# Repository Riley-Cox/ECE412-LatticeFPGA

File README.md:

# ECE412-LatticeFPGA
## WSL Setup
- Install the Terminal app on the Microsoft Store
- Install a Linux Distribution from the Microsoft Store, Debian was used for this project
- Install usbipd through PowerShell by using the following command
  
  ```
  winget install --interactive --exact dorssel.usbipd-win
  ```
- To ensure that it is installed run `usbipd list` , you should see your usb device with its BusID (the UPduino should show up as "serial converter")
- A USB bind is needed. Open Powershell as Admin, then run `usbipd bind --busid <busid>`
- To attach a USB to WSL run `usbipd attach --wsl --busid <busid>`
- In WSL, the device should show up when `lsusb` is ran, if the command is not found run  `sudo apt-get install usbutils `
- To disconnect the device run `usbipd detach --busid <busid>`

## Dependencies
### Ubuntu/Debian
```
sudo apt-get install autoconf automake autotools-dev curl python3 python3-pip python3-tomli libmpc-dev libmpfr-dev libgmp-dev gawk build-essential bison flex texinfo gperf libtool patchutils bc zlib1g-dev libexpat-dev ninja-build git cmake libglib2.0-dev libslirp-dev xxd make
```
### Fedora
```
sudo yum install autoconf automake python3 libmpc-devel mpfr-devel gmp-devel gawk  bison flex texinfo patchutils gcc gcc-c++ zlib-devel expat-devel libslirp-devel xxd make
```
### Arch
```
sudo pacman -Syu autoconf automake curl python3 libmpc mpfr gmp gawk base-devel bison flex texinfo gperf libtool patchutils bc zlib expat libslirp xxd make
```
## RISC-V GNU Toolchain
- From your home directory, clone the RISC-V GNU toolchain from the following repo 

  ```
  git clone https://github.com/riscv/riscv-gnu-toolchain
  ```

- From your home directory, open your shell rc file to edit (`vim .zshrc` or `vim .bashrc`) and add
  ```
  export PATH="<writeable directory>:$PATH"
  ```
  Note that the path you choose for the `<writeable directory>` should end with /bin
  
  Ex: `export PATH="$HOME/Documents/riscv-toolchain/bin:$PATH"`
- Then run `source .zshrc` if using zsh or `source .bashrc` if using bash
  
- `cd` into the riscv-gnu-toolchain directory, run
  ```
  ./configure --prefix=<writeable directory>
  ```
  Note that this `<writeable directory>` does not need to include /bin
  
  Ex: `./configure --prefix=$HOME/Documents/riscv-toolchain`
- then run `make`

## Open Source Toolchain Setup
### Ubuntu/Debian
```
sudo apt-get install yosys fpga-icestorm nextpnr-ice40-qt
```
### Arch
```
yay -S yosys-git icestorm-git nextpnr-git
```
### Fedora
```
sudo dnf install yosys icestorm nextpnr
```

## Building on the UPduino board
- Clone this repo
  ```
  git clone https://github.com/Riley-Cox/ECE412-LatticeFPGA.git
  ```
  
- Navigate to `ECE412-LatticeFPGA/V2.1/src/icicle` 
- Run `make clean`
- Run `make BOARD=upduino`
- Run `sudo iceprog top.bin`

## Migrating Icicle from UPduino V1 to V2.1
- Removed SPI_FLASH define from the upduino-defines.sv file located in `/icicle/boards`
- Changed PROGMEM value from flash to ram in the upduino.mk file located in `/icicle/boards`
- Changed UART RX/TX pins to 15 and 14 respectively in the upduino.pcf file located in `/icicle/boards`
- Created a flash_csn output in icicle.sv and assign it 1 (`assign flash_csn = 1`)

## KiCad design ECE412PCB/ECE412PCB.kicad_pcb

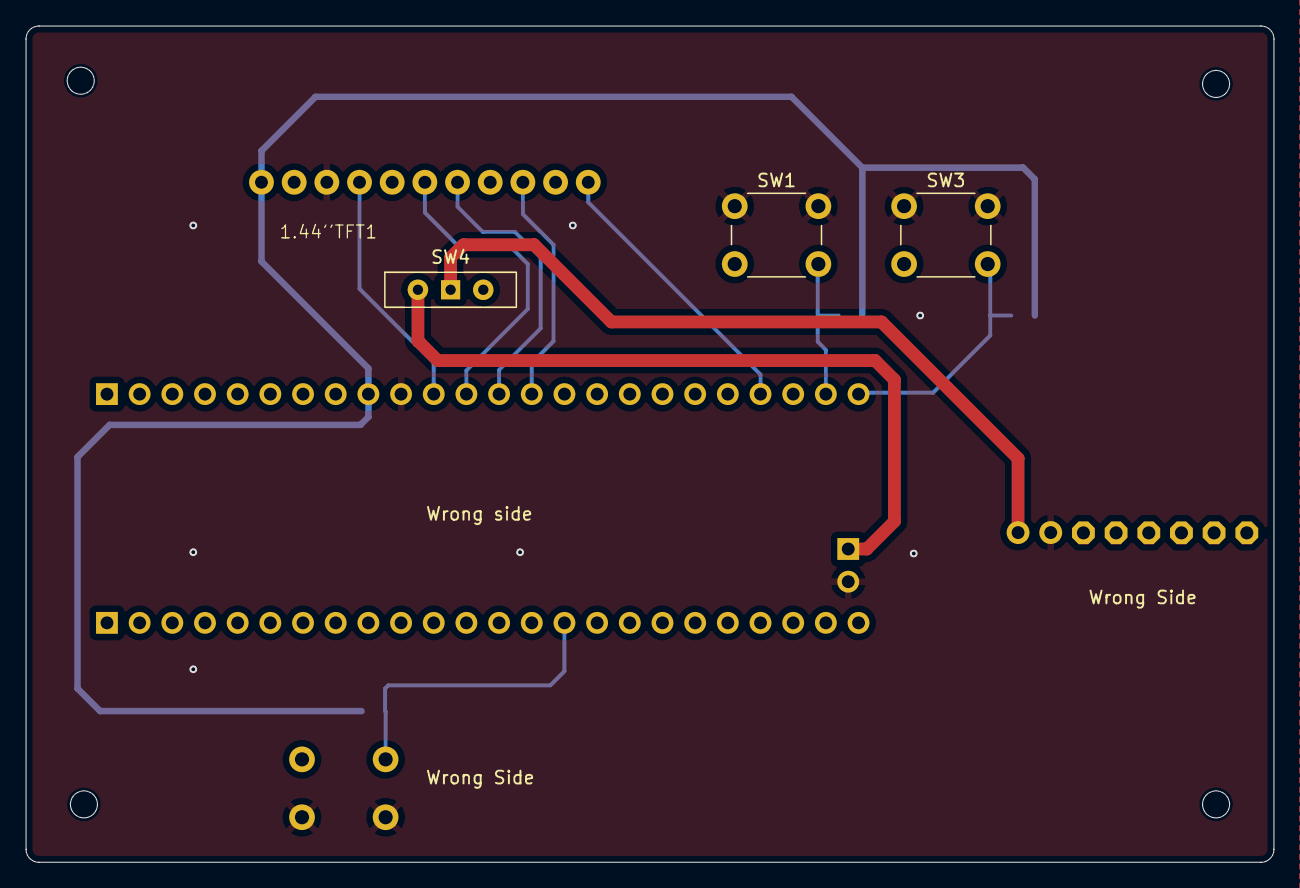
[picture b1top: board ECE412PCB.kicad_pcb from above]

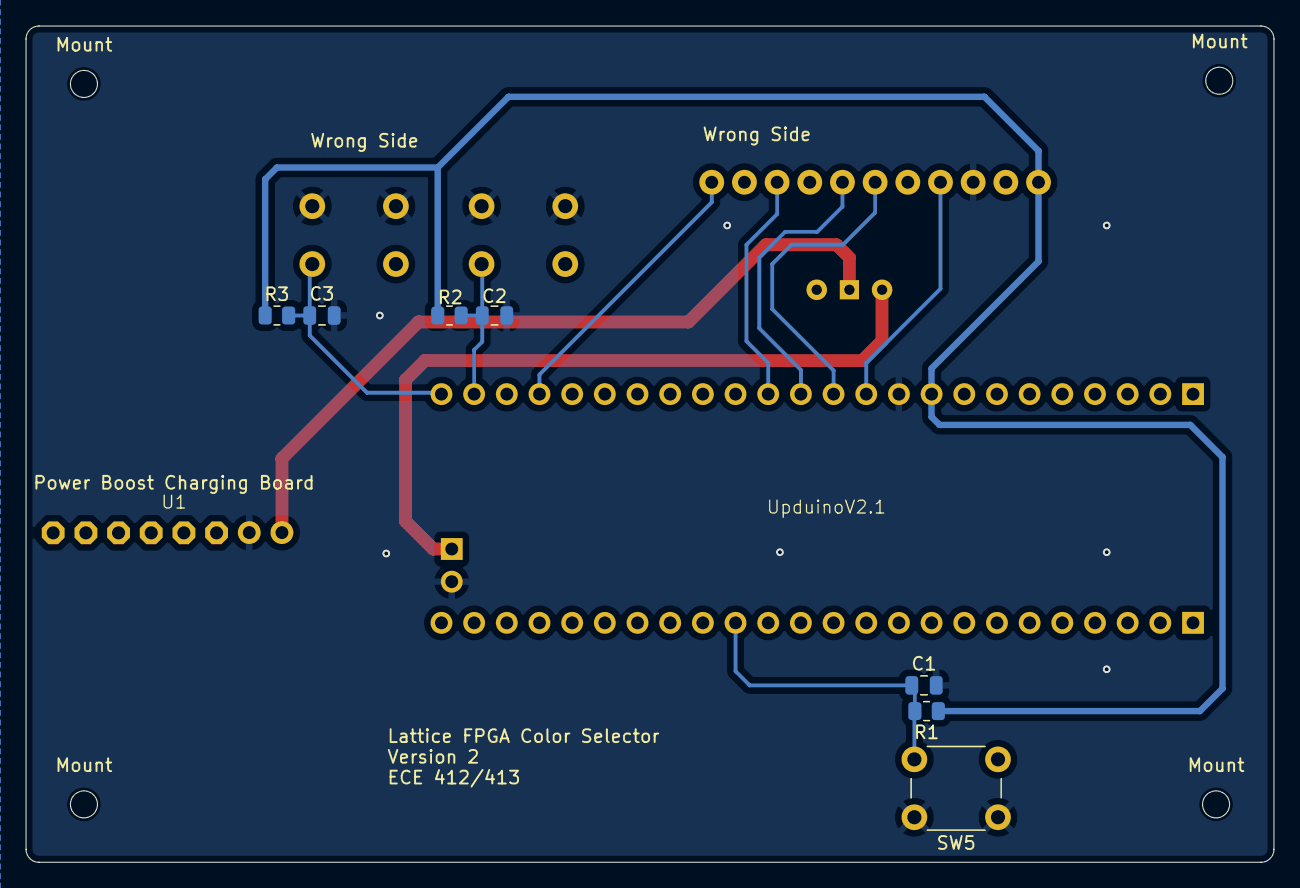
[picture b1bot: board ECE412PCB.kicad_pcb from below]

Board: 2 copper layers, 97.0 x 65.0 mm, 17 parts (9 on the bottom side), 12 nets.

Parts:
1.44''TFT1: 1.44_ TFT Display
C1, C2, C3: C; C_0805_2012Metric
Mount: MountingHole_2.1mm
Mount#2, Mount#3, Mount#4: MountingHole_2.1mm
R1, R2, R3: R; R_0805_2012Metric
SW1, SW3, SW5: SW_Push; SW_PUSH_6mm
SW4: Board Power; SW_Slide-03_Wuerth-WS-SLTV_10x2.5x6.4_P2.54mm
U1: Power Boost Charging Board; PowerBoost-500
UpduinoV2.1: UPduinoV3.1

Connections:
+3.3V: 1.44''TFT1.1 (Vin), R1.1, R2.1, R3.1, UpduinoV2.1.19 (3.3V)
+5V: SW4.1 (A), U1.1 (5V)
/CS: 1.44''TFT1.7 (TCS), UpduinoV2.1.23 (26)
/ColorPush: C2.1, R2.2, SW1.2, UpduinoV2.1.33 (38)
/DC: 1.44''TFT1.9 (D/C), UpduinoV2.1.24 (27)
/LITE: 1.44''TFT1.11 (Lite), UpduinoV2.1.31 (35)
/MOSI: 1.44''TFT1.6 (SI), UpduinoV2.1.22 (25)
/Reset: C1.1, R1.2, SW5.2, UpduinoV2.1.9
/SCK: 1.44''TFT1.4 (SCK), UpduinoV2.1.21 (23)
/brightPush: C3.1, R3.2, SW3.2, UpduinoV2.1.34 (28)
GND: 1.44''TFT1.3 (Gnd), C1.2, C2.2, C3.2, SW1.1, SW3.1, SW5.1, U1.2 (GND), UpduinoV2.1.20 (GND), UpduinoV2.1.35 (GND)
unnamed: SW4.2 (B), UpduinoV2.1.36 (5V)

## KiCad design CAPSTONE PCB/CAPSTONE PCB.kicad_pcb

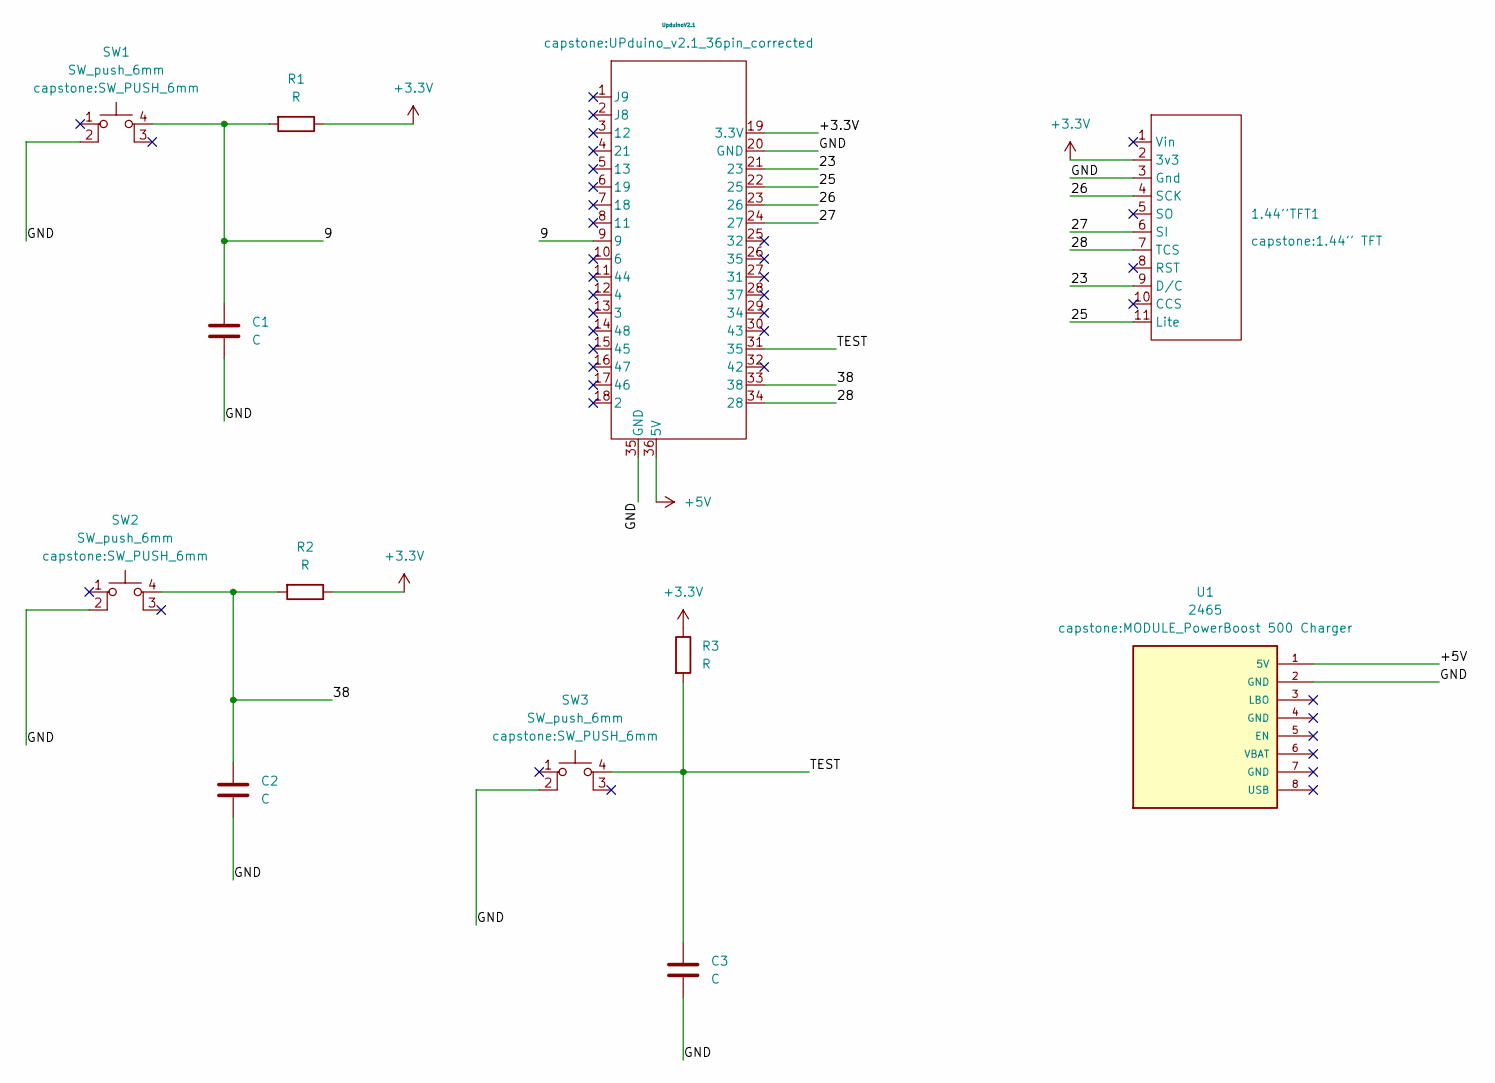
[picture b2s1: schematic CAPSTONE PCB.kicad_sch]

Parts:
1.44''TFT1: 1.44'' TFT
C1, C2, C3: C; C_Axial_L3.8mm_D2.6mm_P7.50mm_Horizontal
R1, R2, R3: R; R_Axial_DIN0207_L6.3mm_D2.5mm_P2.54mm_Vertical
SW1, SW2, SW3: SW_push_6mm; SW_PUSH_6mm
U1: 2465; MODULE_PowerBoost 500 Charger; PARTREV B
UpduinoV2.1: UPduino_v2.1_36pin_corrected

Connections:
+3.3V: 1.44''TFT1.2 (3v3), R1.1, R2.1, R3.1, UpduinoV2.1.19 (3.3V)
+5V: U1.1 (5V), UpduinoV2.1.36 (5V)
/9: C1.1, R1.2, SW1.4 (A), UpduinoV2.1.9
/23: 1.44''TFT1.9 (D/C), UpduinoV2.1.21 (23)
/25: 1.44''TFT1.11 (Lite), UpduinoV2.1.22 (25)
/26: 1.44''TFT1.4 (SCK), UpduinoV2.1.23 (26)
/27: 1.44''TFT1.6 (SI), UpduinoV2.1.24 (27)
/28: 1.44''TFT1.7 (TCS), UpduinoV2.1.34 (28)
/38: C2.1, R2.2, SW2.4 (A), UpduinoV2.1.33 (38)
/GND: 1.44''TFT1.3 (Gnd), C1.2, C2.2, C3.2, SW1.2, SW2.2, SW3.2, U1.2 (GND), UpduinoV2.1.20 (GND), UpduinoV2.1.35 (GND)
/TEST: C3.1, R3.2, SW3.4 (A), UpduinoV2.1.31 (35)

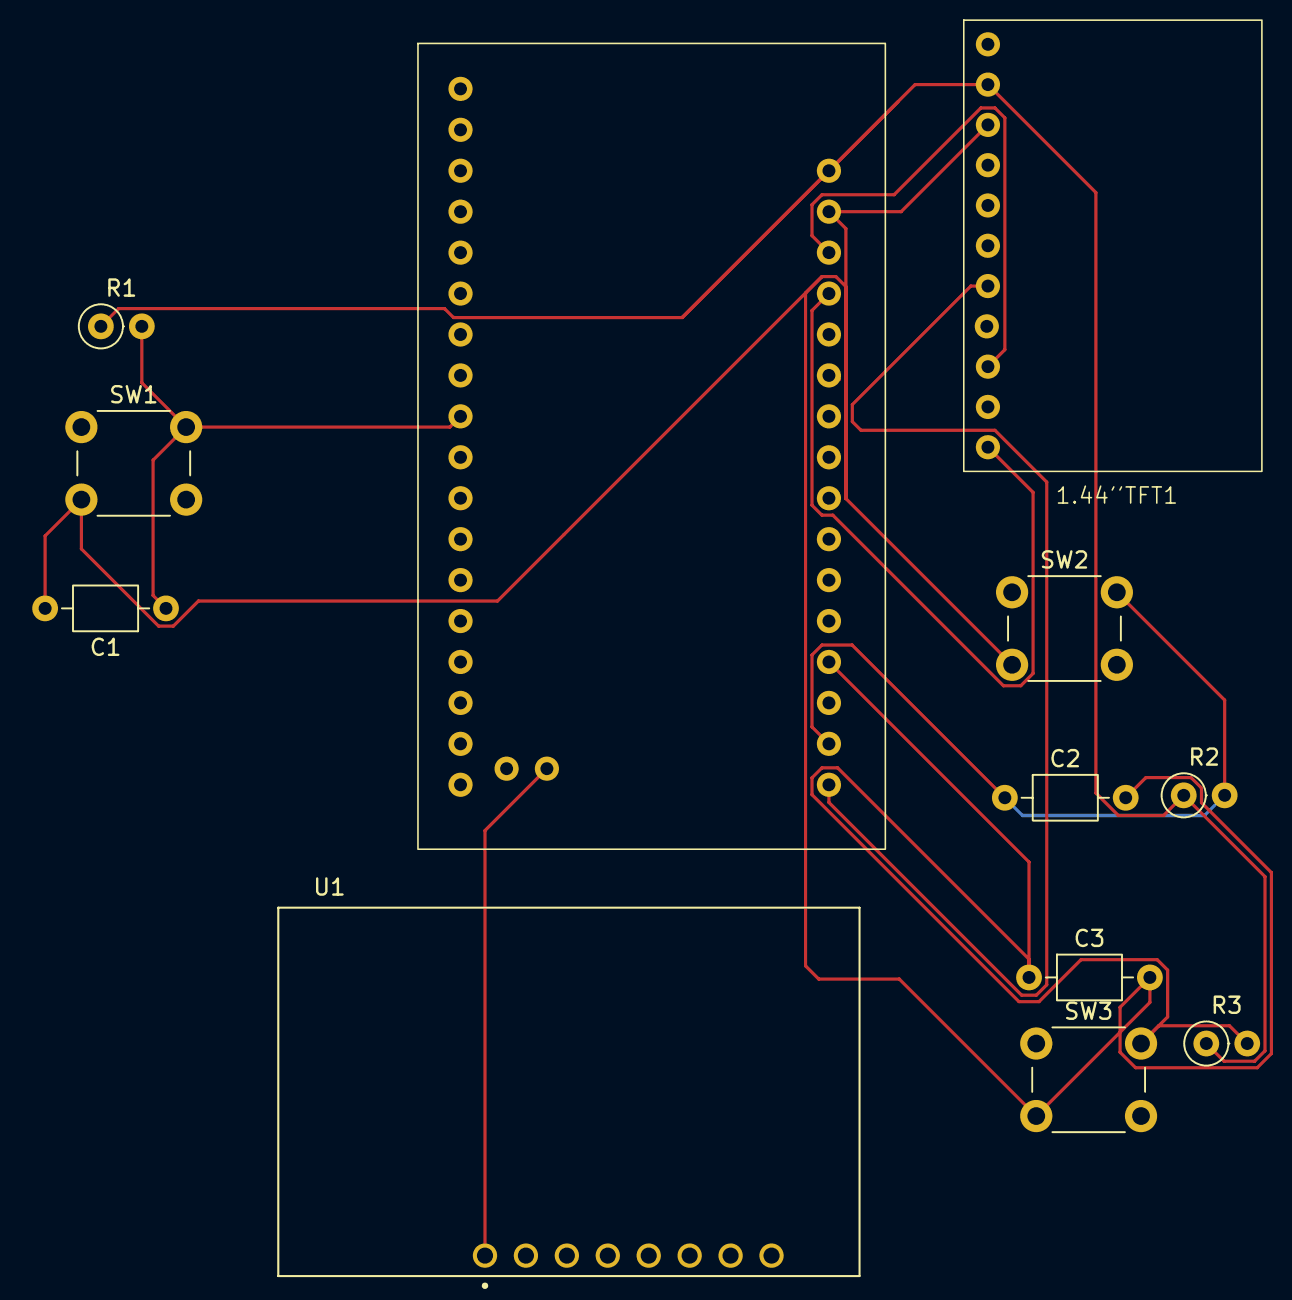
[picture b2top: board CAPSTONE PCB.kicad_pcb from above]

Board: 2 copper layers, 12 parts (0 on the bottom side), 11 nets.

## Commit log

2025-01-20 Weekly Report set up
    Include temple from Andrew, and weekly report. Delete the gray text while finished.
2025-01-20 Set up documents
    Project description and Team Contract
2025-01-20 Create Friday_Jan_17_2025_Meeting_Notes.md
    Added the meeting notes for our initial meeting with Rahul
2025-01-20 Update Friday_Jan_17_2025_Meeting_Notes.md
    Attempting to fix formatting issues
2025-01-20 Update Friday_Jan_17_2025_Meeting_Notes.md
    Fixed remaining formatting issues
2025-01-20 Update Friday_Jan_17_2025_Meeting_Notes.md
    further fix attempted for bullet points
2025-01-20 Update Friday_Jan_17_2025_Meeting_Notes.md
    Final Fix to attendance bullet points
2025-01-20 Adding Meeting Notes (#1)
    * Create Friday_Jan_17_2025_Meeting_Notes.md
    Added the meeting notes for our initial meeting with Rahul
    * Update Friday_Jan_17_2025_Meeting_Notes.md
    Attempting to fix formatting issues
    * Update Friday_Jan_17_2025_Meeting_Notes.md
    Fixed remaining formatting issues
2025-01-24 Added preliminary gannt chart to repo
    *SUBJECT TO CHANGE*
2025-01-24 add rough draft of project proposal
    proposal version 0.1
2025-01-25 Mohammad edits (#2)
    * Create Friday_Jan_17_2025_Meeting_Notes.md
    Added the meeting notes for our initial meeting with Rahul
    * Update Friday_Jan_17_2025_Meeting_Notes.md
    Attempting to fix formatting issues
    * Update Friday_Jan_17_2025_Meeting_Notes.md
    Fixed remaining formatting issues
2025-02-02 Update README.md
    Added changes that need to be made to make Icicle RISC-V core work on UPduino V2.1
2025-02-02 Update README.md (#3)
    Added changes that need to be made to make Icicle RISC-V core work on UPduino V2.1
2025-02-03 Added UPduino V2.1 migration for icicle, now able to build on V2.1 and use serial monitor
2025-02-03 Trying to fix issue
2025-02-03 Adding icicle files
2025-02-08 Create TODO
2025-02-08 Create TODO (#5)
2025-02-10 Update TODO
2025-02-11 Update TODO (#7)
2025-02-11 Update README.md
    Added the ability to copy the long dependency packages and removed the install make and riscv-unknown-elf from the "other dependencies" section. Added make to "Dependencies"
2025-02-17 Create 17FEB2025
    Meeting notes
2025-02-17 Create 17FEB2025 (#9)
    Meeting notes
2025-02-20 Set of param
2025-02-20 Fixed
2025-02-20 Formatted
2025-02-20 Doc sync
2025-02-21 Create 21FEB2025
2025-02-23 3D printing
2025-02-23 Create 21FEB2025 (#10)
2025-02-24 Create 24FEB2025
2025-02-24 Create 24FEB2025 (#11)
2025-02-26 Create testbench_notSyn
2025-02-28 Create 28FEB2025
2025-03-01 Create 28FEB2025 (#13)
2025-03-03 Create 03MAR2025
2025-03-04 Create 03MAR2025 (#14)
2025-03-07 Text display
2025-03-07 Create 07MAR2025
2025-03-08 Update Top_module_spi.sv
    added buffer and clock generation through HSOSC primitive
2025-03-10 Driver code in C, version 0.1
    The first version of code, the values and address in hw.h should be changed based on real hardware
2025-03-10 Create 07MAR2025 (#15)
2025-03-10 Create 10MAR2025
2025-03-10 Update 10MAR2025
2025-03-14 Create 14MAR2025
2025-03-20 Weekly Report updates
2025-03-21 Weekly Reports
2025-03-24 Create 24MAR2025
2025-03-24 Create 14MAR2025 (#16)
2025-03-24 Added yosys changes for spi
2025-03-25 testing file management
2025-03-25 Test didn't work
2025-03-25 Adding in peripheral modules and testbench
2025-03-25 Better yosys synth commands
2025-03-25 Radiant mods
2025-03-26 Create 26MAR2025
2025-03-26 Yosys PLL
2025-03-27 Create 31JAN2025
2025-03-27 Create 13FEB2025
2025-03-27 Create 03FEB2025
2025-03-27 Create 27JAN2025
2025-03-27 Changed Top_module_spi.sv to the version succesfully tested in Radiant
2025-03-27 added reset pullup to fix yosys issue
    added reset pullup to fix yosys issue
2025-03-27 added prelimenary support for spi controller
2025-03-27 add connections for spi controller
2025-03-27 added missing port declerations
2025-03-27 added connections for spi controller
2025-03-27 Fix Syntax Errors
2025-03-27 Added missing declarations for SPI Controller
2025-03-27 Incorporated rv32_mem.sv changes
2025-03-27 Initial integration for SPI module into icicle
2025-03-27 Simple syntax error fixes, build successfully compiles
2025-03-27 Added C program to test spi functionality
2025-03-27 Fixed active low reset for spi
2025-03-27 modified c-program for modularity
2025-03-28 Create 28MAR2025
2025-03-28 Fixed addressing to be within an acceptable range
2025-03-28 fix base address of spi controller to be within acceptable range
2025-03-30 Create SPI_vplan_readme.md
    Need to change the doc with real commands
2025-03-31 remove changes to be used in SPI-MEM
2025-03-31 Remove SPI changes to be used in wrapper
2025-03-31 Create SPI wrapper for peripheral implementation
2025-03-31 Clean up Weekly reports
2025-03-31 Create 31MAR2025
    Notes for 31MAR2025
2025-04-03 Rolled-in spi-mem functionality into spi.sv to unify data and control paths for debugging
2025-04-03 Remove SPI-Mem and instantiate SPI
2025-04-03 Creating GUIDELINE.md
2025-04-04 Fixed missing number 3
2025-04-04 Create folder and temple
    Created the bug report folder and make temple for bug report
2025-04-04 add volatile tag to SPI_BUSY
2025-04-04 04APRIL2025 meeting notes
2025-04-05 nextstate logic changes for spi fsm
2025-04-05 moved around logic inside flipflops
2025-04-05 Some updates
2025-04-05 small changes
2025-04-05 fixed data_reg being used instead of shift_reg
2025-04-05 Added conditional for spi clock counter
2025-04-05 changed clock bit values in fsm
2025-04-05 Uncommented spi_done_ack block in fsm; never left IDLE state
2025-04-06 Added a counter to keep track of shifts
2025-04-06 Better chip select values
2025-04-06 SPI unit test
2025-04-06 Better TB, able to have a zero in MSB
2025-04-06 Created prelimenary merged test file for spi/lcd testing
2025-04-06 Modified st7735_delay_ms implementation to avoid multiplication
2025-04-06 add "-nostdlib -lgcc" to avoid using risc64 linker for libc
2025-04-06 added memcopy declaration and reorganized so it resembles original main.c
2025-04-07 Create 07APR2025
2025-04-08 Removed spi_mem.sv; not using it anymore
2025-04-08 Edit color change methodology
2025-04-08 Add 16-bit output for color module, re-write unit test in top
2025-04-08 Feat/nextstatelogic (#35)
    * Create 31JAN2025
    * Create 13FEB2025
    * Create 27JAN2025
    * Create 03FEB2025
    * Changed Top_module_spi.sv to the version succesfully tested in Radiant
    * Create presynth.sdc
2025-04-08 Add source/unit test for peripherals
2025-04-10 TestDisplay Functions
    Functions to draw and print text and at different sizes, include the functions and a test case
2025-04-11 modified fill_screen to send pixel data in 128 pixel chunks, and altered frame cntrl values to speed up frame transitions on tft
2025-04-11 Changed data types to avoid use of statically linked libraries
2025-04-11 Change dimensions to align with 1.8" tft screen
2025-04-11 WIP button integration; brightness integrated, color button needs work
2025-04-11 Rename 04APRIL2025 to 04APR2025
2025-04-11 Create 11APR2025
2025-04-11 Initial folding-in of text display functionality
2025-04-11 Include function calls to test text display functionality
2025-04-11 Added missing colors for testing
2025-04-11 remove multiplication in fill rectangle function
2025-04-11 fix color values
2025-04-12 First pass button integration
2025-04-12 Moved color logic to dedicated ff block
2025-04-12 Testing ColorSPI
2025-04-12 Color module has color_start
2025-04-14 colorSPI logic fixes
2025-04-14 Fixed some logic issues
2025-04-14 Create 14APR2025
2025-04-14 Removed color_ ouputs
2025-04-14 Removed outputs of internal signals of spi
2025-04-14 Updated for unit testing
2025-04-15 Added test output for button press module
2025-04-17 Added spi.sv and peripheral.sv to test directory
2025-04-17 Testing changes
2025-04-17 Testing for synthesis
2025-04-17 making edited files more accessible
2025-04-17 Added logic to prevent soft lock of software SPI requests
2025-04-17 updated testing files for synthesis
2025-04-18 Added Radiant generated pll
2025-04-18 added missing pll_risc.v in rtl folder
2025-04-18 Added missing pll blackbox module
2025-04-18 add alternative program for testing
2025-04-18 Added self-written pll
2025-04-18 modify top to use self-written pll
2025-04-18 Create 18APR2025
2025-04-21 Create 21APR2025
2025-04-25 Up to date modifications
2025-04-25 Fixed button issue. Fix not suitable for Radiant. SPI color change needs moved to software
2025-04-25 Changed pll to use ipgen instantiation to avoid port routing issues
2025-04-25 Added seperate ipgen file for pll module
2025-04-25 Create 25APR2025
2025-04-25 First draft of using memory for button based transactions
2025-04-25 Added button functionality to C program
2025-04-25 Latching color_start signal
2025-04-25 Adding test signal framework
2025-04-25 Functional color changing
2025-04-25 Added single cycle button signal for brightness
2025-04-25 Create low active push button
2025-04-28 Create 28APR2025
2025-05-02 Cleaned up ugly indentation and ports that were commented out
2025-05-02 Fix Initialization of q to account for linter abuse
2025-05-02 Fix Initialization to account for linter abuse
2025-05-02 added single cycle reset and fed icicle_reset into icicle module
2025-05-03 added verilog file for working pll
2025-05-03 Add configurstion files for working pll
2025-05-03 add misc. files for working pll
2025-05-03 comment out blink to fix synthesis errors due to multiple driver conflict
2025-05-03 switched out to working pll and fixed accidental commenting out of reset_counter logic
2025-05-03 changed clock to be input logic
2025-05-03 revert flash.sv change
2025-05-03 add port for reset
2025-05-05 added clarification for pll_gen.ipx
2025-05-05 Create 05MAY2025
2025-05-05 Create 02MAY2025
2025-05-07 Add single cycle reset for battery functionality
2025-05-09 Added correct single_cycle reset and fixed pll timing issues
2025-05-09 add constraints to setup r and fix timing issues
2025-05-09 Create 09MAY2025
2025-05-12 Fixed synthesis errors, warning need addressed
2025-05-13 Create 12MAY2025
2025-05-15 comment out instr_out at 120 as it is alreaady handeled in reset
2025-05-16 remove multiple drivers of q
2025-05-16 fix initializaition issue for initial address
2025-05-16 map to ram instead of flipflops
2025-05-16 Create 16MAY2025
2025-05-18 changed spi pinouts on upduino
2025-05-19 Create 19MAY2025
2025-05-23 switch ram to primitive based model
2025-05-23 change to lattice primitives in order to correctly map to BRAM
2025-05-23 Fixed duplicate module error
2025-05-23 Create 23MAY2025
2025-05-23 add ram32x ipx
2025-05-23 add progmem ram ipx
2025-05-23 add ram rtl files
2025-05-26 account for behaverial differences between primtive and original model
2025-05-30 fix duplicate rv32_regs module error
2025-05-30 fix multiple driver of q error
2025-05-30 fix partial routing issues due to lack of default cases
2025-05-30 fixed issue where ready out was constantly toggling
2025-05-30 added debug signals for pc monitoring
2025-05-30 add debug signals for pc monitoring
2025-05-30 add pc debug signals and alter method of SSR generation
2025-05-30 change to primitive use for reg so BRAM is used
2025-05-30 add .ipx for ram primitives
2025-05-30 Create 30MAY2025
2025-05-31 Changed button pins
2025-06-01 Added project files
2025-06-01 Added footprint files
2025-06-02 Updated pcf to be the correct pinouts, and added debounce inside button module
2025-06-02 Create 02JUN2025
2025-06-16 Weekly Report update
    12-22
2025-06-17 Update README.md (#44)
2025-06-17 PCF changes to match PCB, RTL button debounce (#43)
    * changed spi pinouts on upduino
    * changed spi pinouts on upduino
    * Changed button pins
    * Updated pcf to be the correct pinouts, and added debounce inside button module
2025-06-17 Upload final report for posterity
